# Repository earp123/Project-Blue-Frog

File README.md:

# nRF5340 LoRa Field-Test Device (SX1262)

An open-source field-test device for **long-distance LoRa radio work**, built
around the Nordic **nRF5340** and a Semtech **SX1262** sub-GHz radio. It
currently hosts the radio layer of a sports-officials intercom: a fixed
4-slot TDMA broadcast flood in which every unit transmits once per frame and
hears everyone else.

Each unit pairs the radio with a local display and an SD card, so it is both
a link **endpoint** and an **instrument**: it runs timed soak tests, shows
live link telemetry, and logs every packet to SD for offline decoding. Build
two to four and you have a real multi-unit link to characterise in the field.

For the design history, measured results and known limitations, see
[CHANGELOG.md](CHANGELOG.md).

## Contents

- [Unit types](#unit-types)
- [Building and flashing](#building-and-flashing)
- [Using a unit](#using-a-unit)
- [Radio parameters](#radio-parameters)
- [LoRa radio shield (TFT unit)](#lora-radio-shield-tft-unit)
- [Rev 2 shield (shield unit)](#rev-2-shield-shield-unit)
- [TFT front end (TFT unit)](#tft-front-end-tft-unit)
- [SDK setup (fresh from Nordic)](#sdk-setup-fresh-from-nordic)

## Unit types

The tree builds one firmware per unit type. Both run the same TDMA radio
layer ([`src/tdma/`](src/tdma)) and the same SD soak logger, on an nRF5340
DK.

| Unit | Hardware | Firmware | Overlay + conf |
|---|---|---|---|
| **TFT unit** | Radio shield (rev 1) on Port 1, plus the Hiletgo ILI9341 TFT breakout (touch + microSD) jumper-wired to Port 0 | `CONFIG_APP_TDMA_CONSOLE`, [`src/tdma_console/`](src/tdma_console) | `boards/nrf5340dk_nrf5340_cpuapp_tft.{overlay,conf}` |
| **Shield unit** | Rev 2 shield: SX1262 + SSD1306 128×32 OLED + microSD in one stack | `CONFIG_APP_TDMA_FIELD`, [`src/tdma_field/`](src/tdma_field) | `boards/nrf5340dk_nrf5340_cpuapp_shield.{overlay,conf}` |

- **TFT unit:** touch + DK-button UI on the TFT. Display-only: no UART.
- **Shield unit:** button-only cycle-menu UI on the OLED. UART logging is on
  over the DK's VCOM.

The two types interoperate on air and can be mixed freely in one kit.

## Building and flashing

Each unit type needs **both** of its files, the overlay and the conf,
passed together. A build with only one of them, or neither, stops at CMake
with these two lines. Use `-p always` (pristine) when switching types.

```sh
# TFT unit
west build -b nrf5340dk/nrf5340/cpuapp -p always -d build-tft -- \
  -DEXTRA_DTC_OVERLAY_FILE=boards/nrf5340dk_nrf5340_cpuapp_tft.overlay \
  -DEXTRA_CONF_FILE=boards/nrf5340dk_nrf5340_cpuapp_tft.conf

# Shield unit
west build -b nrf5340dk/nrf5340/cpuapp -p always -d build-shield -- \
  -DEXTRA_DTC_OVERLAY_FILE=boards/nrf5340dk_nrf5340_cpuapp_shield.overlay \
  -DEXTRA_CONF_FILE=boards/nrf5340dk_nrf5340_cpuapp_shield.conf
```

The board-named radio overlay (`nrf5340dk_nrf5340_cpuapp.overlay`) is applied
automatically in both builds.

**Field runs: one preset image per unit.** Add `-DCONFIG_SOAK_UNIT_SLOT=<0..3>`
after the two files (0 = MASTER, 1–3 = SEC n; one per unit in the kit) and the
unit boots through a splash (unit + TX power) and an SD card check straight
into the soak menu, with no unit pick. On the TFT unit also add
`-DCONFIG_SOAK_TOUCH_CAL=n` to skip the touch calibration and run on the DK
buttons only. `-DCONFIG_SOAK_BOOT_TX_POWER_DBM=<dBm>` changes the boot power
(default +22). For example:

```sh
west build -b nrf5340dk/nrf5340/cpuapp -p always -d build-shield-m --   -DEXTRA_DTC_OVERLAY_FILE=boards/nrf5340dk_nrf5340_cpuapp_shield.overlay   -DEXTRA_CONF_FILE=boards/nrf5340dk_nrf5340_cpuapp_shield.conf   -DCONFIG_SOAK_UNIT_SLOT=0
west build -b nrf5340dk/nrf5340/cpuapp -p always -d build-tft-s2 --   -DEXTRA_DTC_OVERLAY_FILE=boards/nrf5340dk_nrf5340_cpuapp_tft.overlay   -DEXTRA_CONF_FILE=boards/nrf5340dk_nrf5340_cpuapp_tft.conf   -DCONFIG_SOAK_UNIT_SLOT=2 -DCONFIG_SOAK_TOUCH_CAL=n
```

For a **tone soak**, which carries a per-slot audio tone instead of the test
ramp, add `-DCONFIG_SOAK_PAYLOAD_TONE=y` after the two files. Build every unit
in the run that way, then turn any unit's log into a WAV with
[`src/tdma_console/tools/reconstruct_tone.py`](src/tdma_console/tools/reconstruct_tone.py)
(see [`docs/tone_payload_test.md`](docs/tone_payload_test.md)).

**On the bench the SD card is optional.** Both builds include the J-Link RTT
bench port (`CONFIG_SOAK_RTT`). It streams every soak record to the host and
takes commands over the DK's own J-Link USB, driven by
[`src/tdma_console/tools/rtt_link.py`](src/tdma_console/tools/rtt_link.py)
(`pip install pylink-square`):

```sh
rtt_link.py --all capture -o soaks/rtt/ --soak 5   # every unit, 5 min, no cards
```

A capture file is a soak log. The same port uploads a Codec 2 clip and
switches the payload (`mode ramp|tone|clip`). The clip tools are
`c2clip.py` and `reconstruct_c2.py`; see
[`docs/rtt_link_c2_transport.md`](docs/rtt_link_c2_transport.md).

Flash with the DK's J-Link serial number when more than one board is on USB
(`nrfutil device list` shows them):

```sh
west flash -d build-shield --dev-id <serial>
```

> [!NOTE]
> A DK that arrives with readback protection (APPROTECT) refuses to attach.
> `west flash --recover` fixes it once, and **erases all flash on both
> cores**. These builds leave debug access open, so later flashes work
> normally. `west flash` defaults to the `nrfutil` runner, which needs its
> `device` command (`nrfutil install device`); `-r jlink` also works.

## Using a unit

Both types behave the same way:

- **Power-on unit pick (mandatory unless preset).** Choose **MASTER**
  (slot 0) or **SEC 1**, **SEC 2** or **SEC 3**. This sets the role and the
  TX slot together. The master beacons the frame timing, and each secondary
  locks to it. Every unit in a kit needs its own slot. The choice holds until
  reboot. The TFT unit runs a touch calibration first. A unit built with
  `CONFIG_SOAK_UNIT_SLOT` skips both and boots through its splash and an SD
  check into the soak menu.
- **SD check at boot:** `CARD OK` with the log count and free space, or the
  failing step (`mnt -19` is a card with no FAT32/exFAT volume; the firmware
  never formats one). A soak still runs without a card, unlogged.
- **SOAK:** pick 5 min, 30 min, 2 h or continuous. Live pages show elapsed
  time, TX/stale, RX with missed/duplicate frames, phase error and ppm,
  RSSI/SNR, the log file, and the staging-latency gauge. The shield unit
  opens on a summary page: each peer's last RSSI (`--` once quiet for 2 s),
  RX count and loss, TX count and log state.
- **TX power:** −9…+22 dBm, applied from the next packet. Both unit types
  boot at +22 dBm.
- **SD logging:** every soak writes `<PWR>_<DUR>_NNN.BIN` (e.g.
  `P0_5M_000.BIN`) with one 64-byte record per packet (128 bytes in an
  80-byte-payload build, `CONFIG_TDMA_PAYLOAD_LEN=80`,
  docs/opus_payload.md). Decode with
  [`src/tdma_console/tools/decode_soak_log.py`](src/tdma_console/tools/decode_soak_log.py).
  Each file's header records the unit's role and slot.
- **Buttons:** B1 = UP, B2 = DOWN, B3 = OK, B4 = BACK. On the shield unit, B4
  also stops a running soak.

> [!IMPORTANT]
> **Reboot after swapping an SD card.** Card detect is read by the app only,
> so a card changed while mounted is never re-initialised, and every write
> then fails. The shield unit's socket is push-push: it makes no contact
> until it clicks.

## Radio parameters

Fixed in [`src/tdma/tdma.h`](src/tdma/tdma.h); only TX power is adjustable
at runtime.

- Frequency: 915.0 MHz, single channel
- LoRa SF5 / BW 500 kHz / CR 4/5, explicit header, CRC on
- Preamble: 12 symbols (the SX1262 minimum for SF5)
- Packet: 44 bytes (4-byte TDMA header + 40-byte payload), 7,760 µs on air
- Frame: 4 slots × 20 ms = 80 ms. Master in slot 0, secondaries in 1–3.

---

## LoRa radio shield (TFT unit)

The SX1262 (Wio-SX1262) is mounted on a custom Arduino-form-factor shield that
routes its signals to the nRF5340 DK Port 1 header section. The rev 2 shield
keeps exactly the same radio pins.

### Wiring (nRF5340 DK → Wio-SX1262)

| Signal   | nRF5340 pin | Wio-SX1262 pin   |
| -------- | ----------- | ---------------- |
| SPI SCK  | P1.05       | SCK              |
| SPI MOSI | P1.04       | MOSI             |
| SPI MISO | P1.01       | MISO             |
| SPI CS   | P1.07       | NSS              |
| RESET    | P1.06       | RESET            |
| BUSY     | P1.09       | BUSY             |
| DIO1     | P1.08       | DIO1             |
| RF_SW    | P1.00       | RF_SW            |
| VCC      | 3V3         | VCC (+ 33µF cap) |
| GND      | GND         | GND              |

Notes:

- **RF_SW** (P1.00) is the Wio-SX1262 antenna switch's RX enable. The
  firmware drives it HIGH while the radio receives and LOW otherwise; DIO2
  drives the TX side. Held LOW, the receiver hears through the switch's
  isolation, 32 dB down (measured 2026-10-09 on both unit types).
- **DIO2** is internally bridged to TXEN on the Wio-SX1262 — no external wiring.
  `dio2-tx-enable` in the overlay lets the chip drive TXEN itself.
- **DIO3** drives the onboard TCXO — no external wiring; configured via
  `dio3-tcxo-voltage`.
- **uart1** is disabled in the overlay so that P1.01 is free for MISO.
- **33µF decoupling capacitor** on the Wio-SX1262 VCC pin is required. The TX
  current transient on the SX1262 power amplifier causes a supply droop
  sufficient to cause intermittent TX failures without it.

Devicetree (`nrf5340dk_nrf5340_cpuapp.overlay`, SX1262 node):

```dts
lora: sx1262@0 {
    compatible = "semtech,sx1262";
    reg = <0>;
    reset-gpios    = <&gpio1 6 GPIO_ACTIVE_LOW>;
    busy-gpios     = <&gpio1 9 GPIO_ACTIVE_HIGH>;
    dio1-gpios     = <&gpio1 8 GPIO_ACTIVE_HIGH>;
    dio2-tx-enable;
    dio3-tcxo-voltage = <SX126X_DIO3_TCXO_1V8>;
    tcxo-power-startup-delay-ms = <10>;
    spi-max-frequency = <500000>;
};
```

The radio is selected through the `lora0` alias; `RF_SW` is exposed via the
`zephyr,user` node's `rf-sw-gpios` property (P1.00). The native Zephyr driver
only initialises the chip; the TDMA layer owns it after that.

---

## Rev 2 shield (shield unit)

One Arduino-form-factor board carrying the Wio-SX1262 (same pins as above),
a 0.96" SSD1306 OLED and a push-push microSD socket. Fabrication data:
[`Hardware/OLED-SD-SX1262-Shield_2026-08-16.zip`](Hardware/OLED-SD-SX1262-Shield_2026-08-16.zip).
All pins were traced in its netlist and confirmed on the bench.

| Device | Bus | Pins (DK Arduino header) |
|---|---|---|
| microSD | spi4 | SCK **P1.14** (D12), MOSI P1.13 (D11), MISO **P1.15** (D13), CS P1.11 (D9), card-detect P1.12 (D10, active low) |
| SSD1306 128×32 | i2c1 @ 400 kHz | SDA P0.25 (A4), SCL P0.26 (A5), RST P0.07 (A3), address 0x3C |

- **SD SCK/MISO are the reverse of the DK's own `arduino_spi`.** That is how
  the board is routed.
- **The OLED is on A4/A5.** The R3 header's dedicated SDA/SCL pins are not
  connected.
- **No I2C pull-ups on the shield.** The overlay enables the nRF's internal
  ones as a fallback.
- **The I2C driver's concat buffer is raised to 1025 bytes** (a control byte
  plus a full frame). With the 16-byte default, every frame write fails and
  the screen stays blank.

---

## TFT front end (TFT unit)
[https://a.co/d/047jULLv](url)
The TFT unit's front end — ILI9341 TFT, XPT2046 touch, microSD — shares one
SPI bus (**spi4**, the DK's high-speed `arduino_spi` instance on Port 0),
distinct from the radio's spi2 on Port 1. Each device has its own chip
select. **These signals are jumper-wired to the DK Arduino headers.**

### Pin assignments

| Signal        | nRF5340 pin | Device pin                       |
| ------------- | ----------- | -------------------------------- |
| SPI SCK       | P0.13       | SCK (all)                        |
| SPI MOSI      | P0.14       | MOSI/SDI (all)                   |
| SPI MISO      | P0.15       | MISO/SDO (all)                   |
| LCD CS        | P0.16       | ILI9341 CS                       |
| LCD D/C       | P0.17       | ILI9341 D/C                      |
| LCD RESET     | P0.18       | ILI9341 RESET                    |
| LCD backlight | P0.31       | Backlight (active high)          |
| TOUCH CS      | P0.28       | XPT2046 CS                       |
| TOUCH IRQ     | P0.29       | XPT2046 IRQ (active low, pull-up)|
| SD CS         | P0.10       | microSD CS                       |

CS lines are indexed by each device's `reg` on the spi4 node: reg 0 = display
(P0.16), reg 1 = touch (P0.28), reg 2 = SD (P0.10).

> [!IMPORTANT]
> **nRF5340 DK board modifications required.** Several of these Port 0 pins are
> wired to on-board peripherals on the DK and must be freed before the front end
> works. The relevant solder bridges are marked on the DK silkscreen (and
> detailed in the nRF5340 DK Hardware User Guide); the exact `SBxx` designators
> vary by board revision.
>
> - **SPI bus — P0.13–P0.18 are shared with the on-board QSPI flash** (MX25R64).
>   SPI SCK/MOSI/MISO and LCD CS / D-C / RESET land on the flash's
>   `QSPI_IO0/IO1/IO2/IO3` + `QSPI_SCK`/`QSPI_CSN`, so the flash must be
>   **disconnected** (cut its solder bridges) — otherwise it loads and contends on
>   the shared bus.
> - **P0.28–P0.31 are the four on-board LEDs** (LED1–LED4). The front end uses
>   P0.28 (touch CS), P0.29 (touch IRQ), and P0.31 (backlight); P0.30 (LED3) is
>   unused. Isolate these LEDs from the GPIOs (per the silkscreen bridges) so the
>   on-board LEDs don't interfere with the touch/backlight lines.
>
> The four DK buttons (P0.23/24/08/09) are **not** modified — they still drive the
> menu UI.

### Implementation notes / deviations

- **Touch binding is** `xptek,xpt2046` (not `ti,tsc2046`) in this Zephyr. It
  reports via the input subsystem (`INPUT_ABS_X/Y`, `INPUT_BTN_TOUCH`); the
  IRQ is edge-to-active (falling, `GPIO_ACTIVE_LOW | GPIO_PULL_UP`).
- **ILI9341 RESET is active-low.** The MIPI-DBI driver leaves reset de-asserted
  after its pulse, so `reset-gpios` must be `GPIO_ACTIVE_LOW` — otherwise the
  panel is held in reset and stays blank even though SPI writes "succeed".
- **CFB cannot drive the ILI9341.** Zephyr's character framebuffer is
  monochrome-only (1 bpp); the ILI9341 is RGB565/RGB888. The app enables CFB only
  to link its (correct) bundled font glyph data, then blits that into RGB565
  itself with `display_write()` (white/black, byte-order agnostic).
- The display uses the **MIPI DBI** subsystem: a `zephyr,mipi-dbi-spi`
  controller wraps spi4 and owns the D/C and RESET sidebands; the
  `ilitek,ili9341` node sits under it.
- **Drawing stays single-owner.** Input callbacks only set atomics; the main
  loop does every `display_write()`. Touch taps are debounced (one event per
  press, release required) before the loop consumes them.
- **Touch is calibrated by an on-device affine fit**
  (`src/tdma_console/touch_cal.c`). Raw XPT2046 coordinates are offset /
  swapped / inverted relative to the display; a 6-parameter affine corrects
  all of it at once. Calibration is a mandatory power-on step: five crosshair
  taps, a least-squares fit, then a verify step. The fit lives in RAM only.

---

## SDK setup (fresh from Nordic)

This project uses the **native** Zephyr SX126x LoRa driver
(`CONFIG_LORA_MODULE_BACKEND_NATIVE` / `CONFIG_LORA_SX126X_NATIVE`), which is
**not part of stock NCS v3.2.1**. Two repo assets close that gap so the project
builds against a clean SDK:

- `external/zephyr-lora-driver/` — the newer Zephyr `drivers/lora/`
  subsystem (incl. the native SX126x driver), vendored verbatim.
- `patches/` — small compat patches: SPI macro arity (`0001`), the
  `regulator-ldo` / `force-ldro` binding properties (`0002`), and the newer
  `lora.h` API the driver expects (`0003`).

### Onboarding (what to do with a fresh Nordic SDK)

1. Install **NCS v3.2.1 + toolchain** via nRF Connect for Desktop → *Toolchain
   Manager* (provides `west`, CMake, Ninja, the Zephyr SDK/GCC). Install
   **SEGGER J-Link** too (the DK's on-board debugger).

2. Prepare the SDK from this repo (idempotent; defaults `ZEPHYR_BASE` to
   `C:/ncs/v3.2.1/zephyr`):

   ```sh
   ZEPHYR_BASE=/path/to/ncs/zephyr ./scripts/setup_sdk.sh
   ```

   This swaps the vendored `drivers/lora/` into the SDK (backing up the stock
   one to `drivers/lora.stock.bak`) and applies the patches.

3. Build one of the two unit types and flash it, as shown in
   [Building and flashing](#building-and-flashing).

**Symptoms if the SDK was not prepared:**

- `macro "SPI_DT_SPEC_INST_GET" requires 3 arguments, but only 2 given`
- `'..._P_regulator_ldo' undeclared` / `'..._P_force_ldro' undeclared`
- silently building the wrong LoRa backend (the native `CONFIG_*` symbols
  don't exist on a clean SDK and are dropped with a warning)

> [!WARNING]
> These changes live in the NCS install, not in this repo. Any `west update`,
> SDK reinstall, or Toolchain Manager repair reverts them — just re-run
> `scripts/setup_sdk.sh` and do a pristine build. Patch 2 changes a
> devicetree binding, which is only picked up on a CMake reconfigure
> (`-p always`).

---

## Third-party code

| Path | What | Licence | Linked into |
|---|---|---|---|
| `external/zephyr-lora-driver/` | Zephyr's newer `drivers/lora/` (native SX126x) | Apache-2.0 | every build (through the SDK) |
| `external/codec2/` | Codec 2 speech codec, subset | LGPL-2.1 | `CONFIG_SOAK_C2_ENCODE` builds only (test firmware; product licensing not settled) |
| `external/speexdsp/` | SpeexDSP preprocessor (noise suppression + AGC), subset | BSD-3-Clause | `CONFIG_SOAK_MIC_DSP` builds ([`docs/mic_dsp_frontend.md`](docs/mic_dsp_frontend.md)) |

Each directory's README says where it came from and what was changed.

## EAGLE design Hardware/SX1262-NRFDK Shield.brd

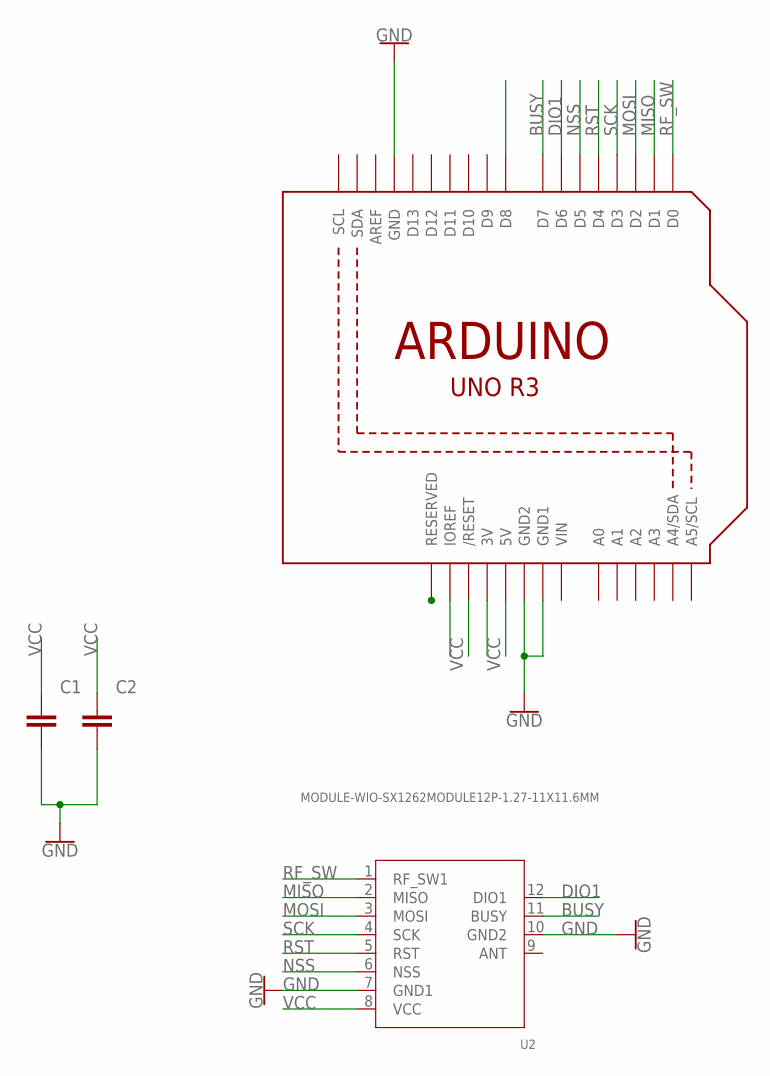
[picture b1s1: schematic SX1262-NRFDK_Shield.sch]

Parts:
C1, C2: C_CHIP-0805(2012-METRIC); CAPC2012X110
U1: ARDUINOR3-BPLACE
U2: MODULE-WIO-SX1262MODULE12P-1.27-11X11.6MM; MODULE12P-1.27-11X11.6MM

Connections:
BUSY: U1.D7, U2.11 (BUSY)
DIO1: U1.D6, U2.12 (DIO1)
GND: C1.2, C2.2, U1.GND, U1.GND1, U1.GND2, U2.7 (GND1), U2.10 (GND2)
MISO: U1.D1, U2.2 (MISO)
MOSI: U1.D2, U2.3 (MOSI)
NSS: U1.D5, U2.6 (NSS)
RF_SW: U1.D0, U2.1 (RF_SW1)
RST: U1.D4, U2.5 (RST)
SCK: U1.D3, U2.4 (SCK)
VCC: C1.1, C2.1, U1.3V, U1.IOREF, U1.RESERVED, U2.8 (VCC)
VIN: U1.VIN

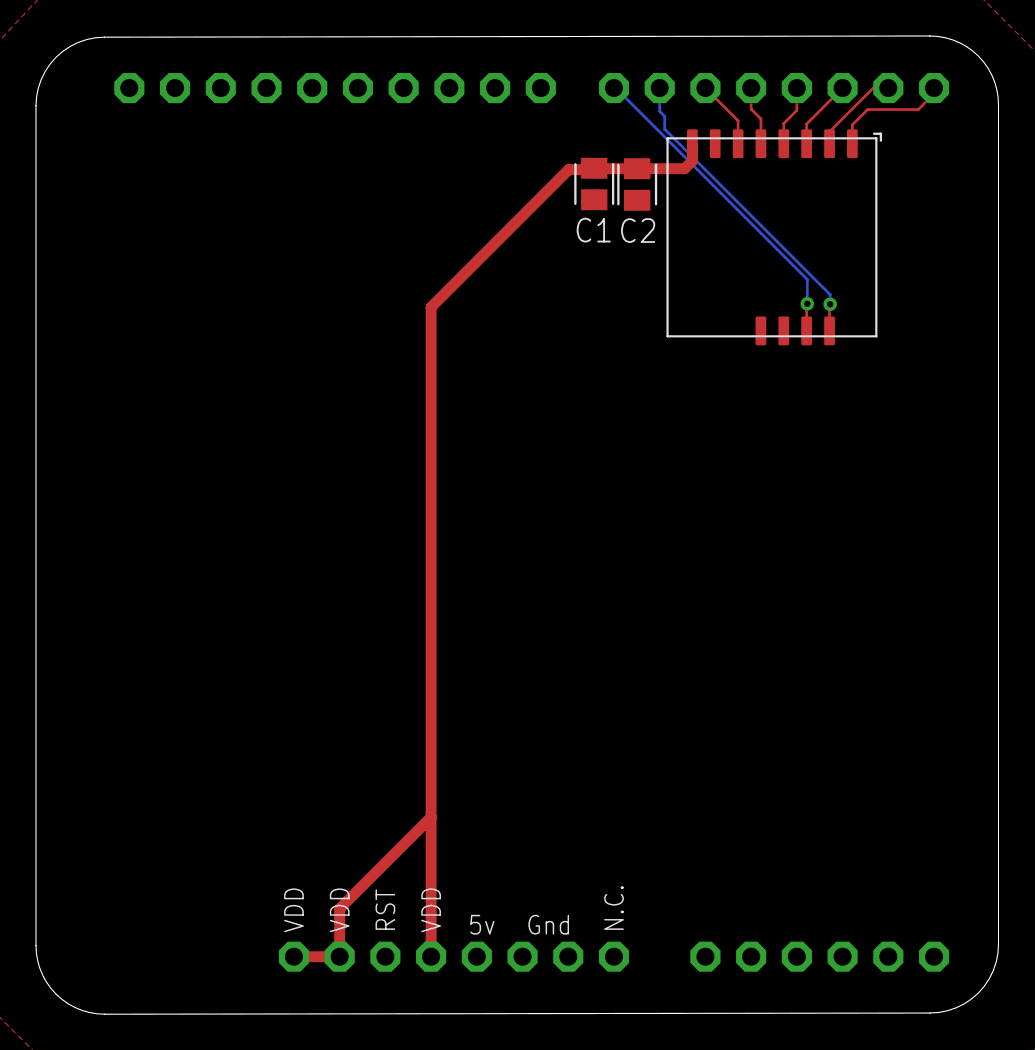
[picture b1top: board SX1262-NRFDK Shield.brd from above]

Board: 2 copper layers, 53.5 x 54.3 mm, 4 parts (0 on the bottom side), 10 nets.

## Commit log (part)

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2026-06-28 Initial commit
    TODO build out rest of menu and tool kit
2026-06-28 touch input config added
    continuing to build out the UI
2026-06-29 Added the ping pong sketch
    Constant RX mode with asynchronous transmit "ping", immediate "pong" response.
2026-06-29 added changelog
2026-06-29 Add images to README for better visualization
    Added images to enhance the README documentation.
2026-06-29 Fix link in README for display/touch/SD front end
    Updated link for display/touch/SD front end section.
2026-06-29 Remove telemetry console behaviour details
    Removed detailed telemetry console behaviour section from README.
2026-06-29 Update README instructions
2026-06-29 Add hardware entry file
2026-06-29 EAGLE Files for the SX1262 Shield
    Dead-simple Arduino shield for quickly attaching the SX1262 to an NRF DK.
2026-06-29 Update hardware entry file with assembly details
    Added additional information about hardware assembly.
2026-06-29 DK solder bridge instructions

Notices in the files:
parts and their libraries:
SparkFun-PowerSymbols: Licensing: Creative Commons ShareAlike 4.0 International - https://creativecommons.org/licenses/by-sa/4.0
